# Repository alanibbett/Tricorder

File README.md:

# Tricorder
Code base for the Day-Zero Tricorder

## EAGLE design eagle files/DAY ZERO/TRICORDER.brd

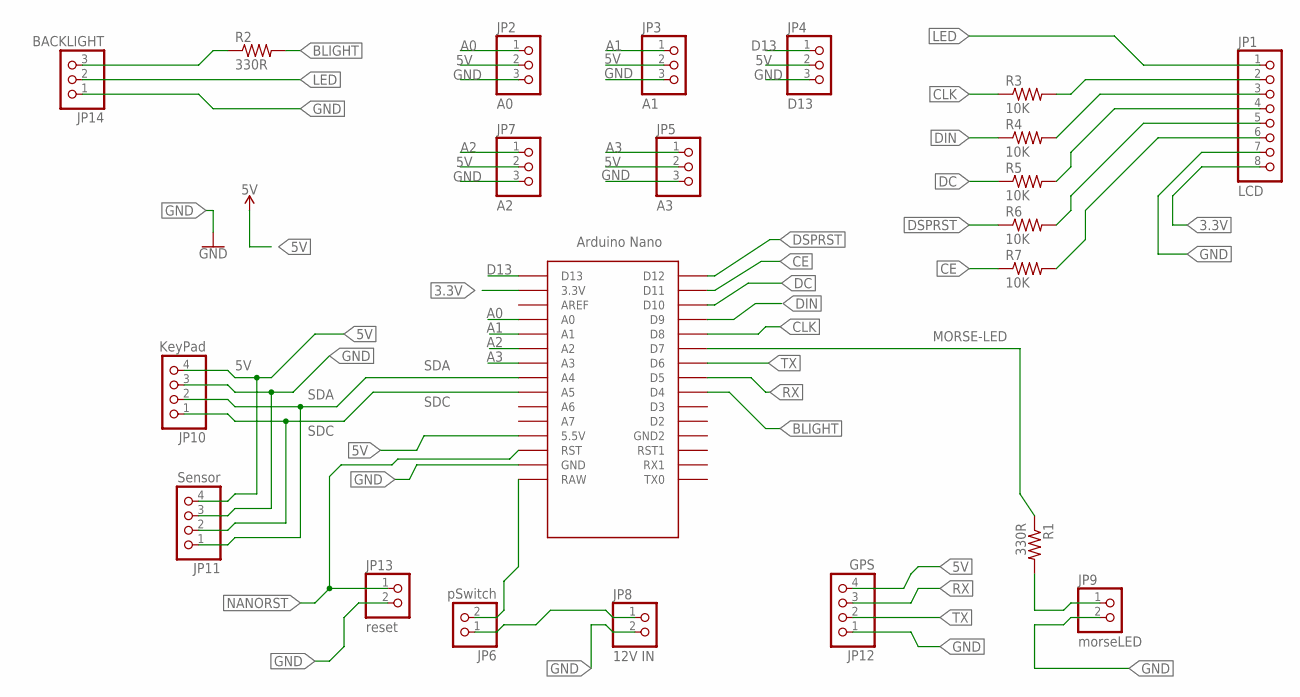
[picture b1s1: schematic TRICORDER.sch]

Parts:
JP1: LCD; 1X08/90
JP2: A0; 1X03
JP3: A1; 1X03
JP4: D13; 1X03
JP5: A3; 1X03
JP6: pSwitch; 1X02/90
JP7: A2; 1X03
JP8: 12V IN; 1X02/90
JP9: morseLED; 1X02/90
JP10: KeyPad; 1X04/90
JP11: Sensor; 1X04/90
JP12: GPS; 1X04/90
JP13: reset; 1X02/90
JP14: BACKLIGHT; 1X03/90
R1, R2: 330R; 0207/9
R3, R4, R5, R6, R7: 10K; 0207/9
U$1: NANO

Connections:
3.3V: JP1.8, U$1.3.3V
5V: JP2.2, JP3.2, JP4.2, JP5.2, JP7.2, JP10.4, JP11.4, JP12.4, U$1.5V (5.5V)
12V: JP6.1, JP8.1
12VS: JP6.2, U$1.RAW
A0: JP2.1, U$1.A0
A1: JP3.1, U$1.A1
A2: JP7.1, U$1.A2
A3: JP5.1, U$1.A3
BLIGHT: R2.2, U$1.D4
CE: R7.1, U$1.D11
CLK: R3.1, U$1.D8
D13: JP4.1, U$1.D13
DC: R5.1, U$1.D10
DIN: R4.1, U$1.D9
DSPRST: R6.1, U$1.D12
GND: JP1.7, JP2.3, JP3.3, JP4.3, JP5.3, JP7.3, JP8.2, JP9.2, JP10.3, JP11.3, JP12.1, JP13.2, JP14.1, U$1.GND
LED: JP1.1, JP14.2
MORSE-LED: R1.1, U$1.D7
unnamed: JP9.1, R1.2
unnamed: JP14.3, R2.1
unnamed: JP1.2, R3.2
unnamed: JP1.3, R4.2
unnamed: JP1.4, R5.2
unnamed: JP1.5, R6.2
unnamed: JP1.6, R7.2
NANORST: JP13.1, U$1.RST
RX: JP12.3, U$1.D5
SDA: JP10.2, JP11.1, U$1.A4
SDC: JP10.1, JP11.2, U$1.A5
TX: JP12.2, U$1.D6

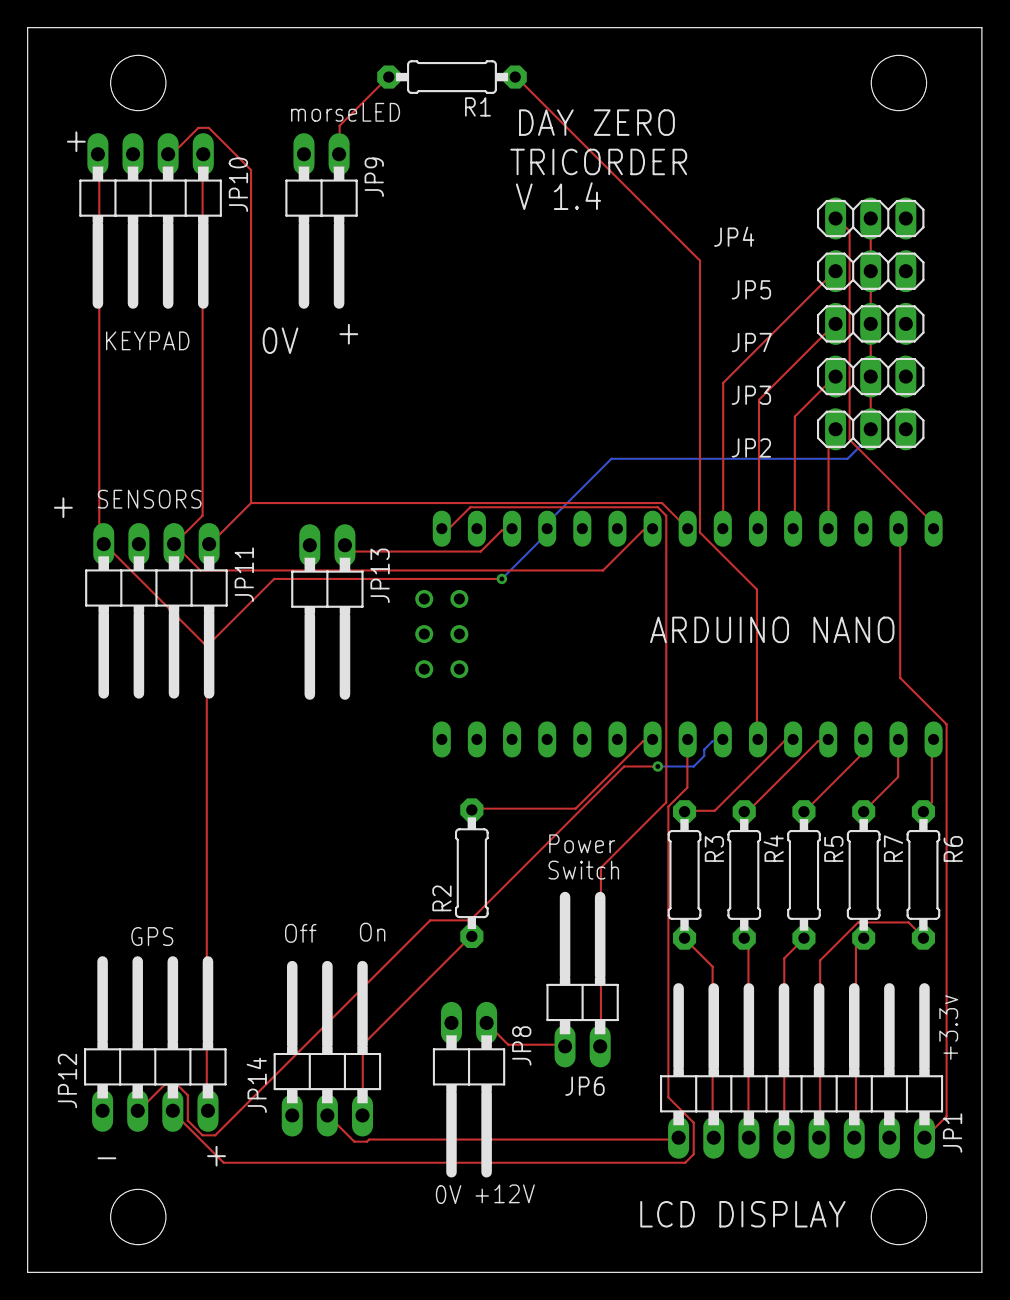
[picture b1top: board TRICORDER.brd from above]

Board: 2 copper layers, 69.0 x 90.0 mm, 22 parts (0 on the bottom side), 30 nets.

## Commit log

2017-10-10 Initial sketch files
2017-10-10 Created description of the prototype code
2017-10-10 Rename Prototype/DayZeroTricorder.ino to Prototype/DayZeroTricorder/DayZeroTricorder.ino
2017-10-10 These libraries are modifications of standard ones and are required

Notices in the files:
parts and their libraries:
SparkFun-PowerSymbols: Licensing: Creative Commons ShareAlike 4.0 International - https://creativecommons.org/licenses/by-sa/4.0
